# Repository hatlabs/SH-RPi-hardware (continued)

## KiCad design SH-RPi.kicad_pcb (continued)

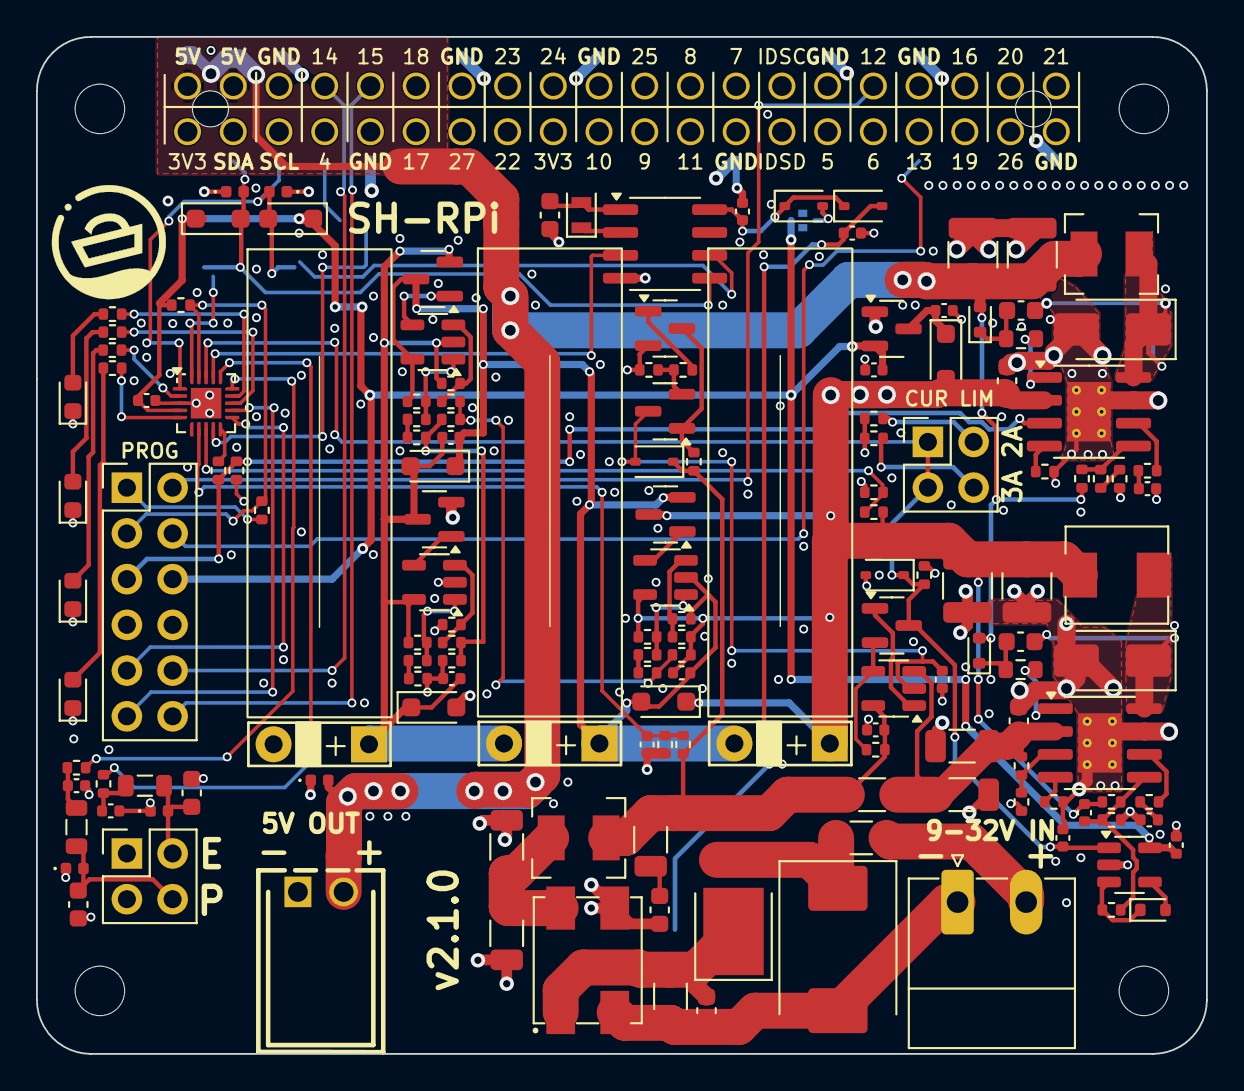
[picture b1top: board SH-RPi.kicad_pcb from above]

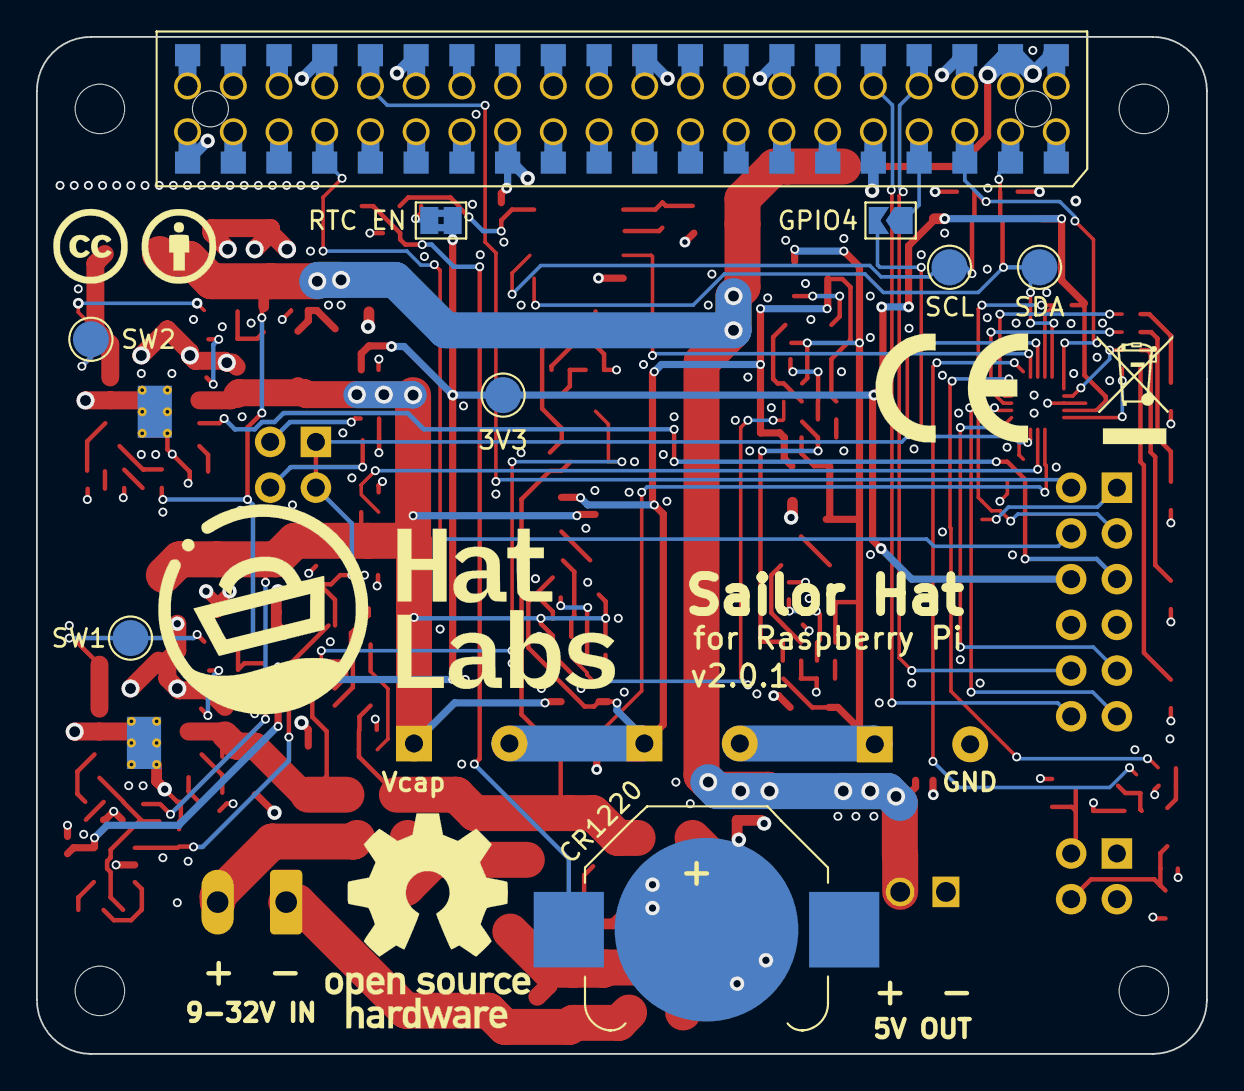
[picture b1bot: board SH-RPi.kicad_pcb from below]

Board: 4 copper layers, 65.0 x 56.5 mm, 168 parts (14 on the bottom side), 92 nets.

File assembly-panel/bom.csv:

Comment,Designator,Footprint,LCSC
Conn_01x02,J101,"Connector_Phoenix_MC:PhoenixContact_MC_1,5_2-G-3.81_1x02_P3.81mm_Horizontal",C8387
100nF,"C305,C306,C311,C312,C403,C406,C803,C1001,C1002,C1003",Capacitor_SMD:C_0402_1005Metric,C1525
10k,"R303,R311,R407,R409",Resistor_SMD:R_0402_1005Metric,C25744
56k,R401,Resistor_SMD:R_0402_1005Metric,C25796
2k,R404,Resistor_SMD:R_0402_1005Metric,C4109
20k,R403,Resistor_SMD:R_0402_1005Metric,C25765
150k,"R402,R1005,R1008,R1011",Resistor_SMD:R_0402_1005Metric,C93947
33pF 50V,"C401,C402",Capacitor_SMD:C_0603_1608Metric,C1663
33pF,"C404,C405",Capacitor_SMD:C_0402_1005Metric,C1562
GZ2012D601TF,"FB401,FB402",Inductor_SMD:L_0805_2012Metric,C1017
100R,"R308,R405,R406",Resistor_SMD:R_0402_1005Metric,C25076
ESD5451N,"D401,D402,D501,D503,D505",Diode_SMD:D_0402_1005Metric,C2936977
Conn_02x06_Odd_Even,J402,Connector_PinHeader_2.54mm:PinHeader_2x06_P2.54mm_Vertical,C5383107
1k,"R206,R408,R501,R502,R503,R504",Resistor_SMD:R_0402_1005Metric,C11702
100k,"R302,R410",Resistor_SMD:R_0402_1005Metric,C25741
ATtiny1616-MNR,U401,Package_DFN_QFN:VQFN-20-1EP_3x3mm_P0.4mm_EP1.7x1.7mm,C507118
Conn_02x02_Top_Bottom,J401,Connector_PinHeader_2.54mm:PinHeader_2x02_P2.54mm_Vertical,C492419
100nF,"C203,C308",Capacitor_SMD:C_0603_1608Metric,C14663
SLO0530H3R3MTT,L301,SH-RPi:L_MWSA0503S,C325963
47uF 16V,"C309,C310",Capacitor_SMD:C_1210_3225Metric,C77101
47k,R313,Resistor_SMD:R_0402_1005Metric,C25792
470k,R312,Resistor_SMD:R_0402_1005Metric,C137976
10m,R301,Resistor_SMD:R_1206_3216Metric,C105362
1N4148WT,"D201,D302,D305",Diode_SMD:D_SOD-523,C414017
5.1R,"R202,R309",Resistor_SMD:R_0603_1608Metric,C25197
68k,"R204,R307",Resistor_SMD:R_0402_1005Metric,C137947
SS56FL,D303,Diode_SMD:D_SMA,C122865
1uF 50V,C303,Capacitor_SMD:C_0603_1608Metric,C15849
10uF 50V,"C301,C302,C702,C703,C704,C705",Capacitor_SMD:C_1206_3216Metric,C13585
510R,R305,Resistor_SMD:R_0402_1005Metric,C25123
RT6365,"U201,U301",Package_SO:SOIC-8-1EP_3.9x4.9mm_P1.27mm_EP2.41x3.3mm_ThermalVias,C3024482
COS1333TR,U302,Package_TO_SOT_SMD:SOT-23-5,C693072
LMV321-TR,"U303,U1001,U1002,U1003",Package_TO_SOT_SMD:SOT-23-5,C3014306
1.5k,R310,Resistor_SMD:R_0402_1005Metric,C25867
BZT52C3V3S,"D301,D304",Diode_SMD:D_SOD-323,C173439
Conn_02x02,J301,Connector_PinHeader_2.54mm:PinHeader_2x02_P2.54mm_Vertical,C492419
3.9k,R316,Resistor_SMD:R_0402_1005Metric,C131467
300k,"R304,R1004,R1007,R1010,R1014,R1016,R1018",Resistor_SMD:R_0402_1005Metric,C25774
3.3k,R314,Resistor_SMD:R_0402_1005Metric,C25890
470pF,C304,Capacitor_SMD:C_0402_1005Metric,C1537
7.5k,R315,Resistor_SMD:R_0402_1005Metric,C137934
SW1,TP301,TestPoint:TestPoint_Pad_D2.0mm,
220nF,C307,Capacitor_SMD:C_0402_1005Metric,C16772
MMBT5551,"Q301,Q302",Package_TO_SOT_SMD:SOT-23,C2145
LBSS84LT1G,Q303,Package_TO_SOT_SMD:SOT-23,C8492
MBRA340T3G-FS,D202,Diode_SMD:D_SMA,C5563736
47uF 6.3V,"C204,C205",Capacitor_SMD:C_1210_3225Metric,C77101
51k,R201,Resistor_SMD:R_0402_1005Metric,C25794
27k,R203,Resistor_SMD:R_0402_1005Metric,C25771
4.7uF,C201,Capacitor_SMD:C_0603_1608Metric,C19666
3.3nF,C202,Capacitor_SMD:C_0402_1005Metric,C26404
FXL0420-1R0-M,"L201,L702",SH-RPi:L_MWSA0402,C167203
12k,R205,Resistor_SMD:R_0402_1005Metric,C25752
SW2,TP201,TestPoint:TestPoint_Pad_D2.0mm,
22pF C0G,C802,Capacitor_SMD:C_0603_1608Metric,C1653
1uF,C801,Capacitor_SMD:C_0402_1005Metric,C52923
Bridged,JP801,Jumper:SolderJumper-2_P1.3mm_Bridged2Bar_Pad1.0x1.5mm,
1N4148WS,"D801,D802",Diode_SMD:D_SOD-323,C2128
PCF8563T,U801,Package_SO:SOIC-8_3.9x4.9mm_P1.27mm,C7440
Conn_01x03,J801,SH-RPi:BatteryHolder_Myoung_MY-1220-03,C964818
X1A000061000200,Y801,Crystal:Crystal_SMD_2012-2Pin_2.0x1.2mm,C55208
5.0SMDJ33CA,D701,Diode_SMD:D_SMC,C2913642
12T.40000063AG12S1B02,F701,Fuse:Fuse_1206_3216Metric,C140479
1R,R701,Capacitor_SMD:C_0603_1608Metric,C22936
100nF 50V,C701,Capacitor_SMD:C_0603_1608Metric,C14663
PCAQ7060MW-102,L701,SH-RPi:L_CMF7060F,C2915648
10S45SP,D702,SH-RPi:SS5U100_TO-277,C2988031
Raspberry_Pi_2_3,J501,SH-RPi:PassthroughPinSocket_FH-00339_2x40_P2.54mm_Vertical_Bottom,C2685112
WHITE LED,"D506,D507,D508,D509",LED_SMD:LED_0603_1608Metric,C434422
Open,JP501,Jumper:SolderJumper-2_P1.3mm_Open_TrianglePad1.0x1.5mm,
1N5819WS,"D502,D504,D901,D1001,D1002,D1003",Diode_SMD:D_SOD-323_HandSoldering,C191023
Conn_01x02,J502,HL_Connector:CONN-TH_2P-P2.54_CONN-TH_2P-P2.54_,C2927503
SCL,TP502,TestPoint:TestPoint_Pad_D2.0mm,
SDA,TP501,TestPoint:TestPoint_Pad_D2.0mm,
1uF 16V,C901,Capacitor_SMD:C_0402_1005Metric,C52923
10uF 6.3V,C902,Capacitor_SMD:C_0402_1005Metric,C15525
3V3,TP901,TestPoint:TestPoint_Pad_D2.0mm,
HT7533-1,U901,Package_TO_SOT_SMD:SOT-23,C5279052
33k,"R1001,R1002,R1003",Resistor_SMD:R_0402_1005Metric,C25779
120k,"R1006,R1009,R1012",Resistor_SMD:R_0402_1005Metric,C93945
SS8050,"Q1001,Q1002,Q1003",Package_TO_SOT_SMD:SOT-23,C2150
330k,"R1013,R1015,R1017",Resistor_SMD:R_0402_1005Metric,C25778

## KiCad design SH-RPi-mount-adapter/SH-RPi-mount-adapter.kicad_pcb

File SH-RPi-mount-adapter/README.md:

# SH-RPi mount adapter

This directory contains a design for a Raspberry Pi mounting adapter. The adapter can be mounted to an enclosure using 3mm diameter adhesive standoffs. The Raspberry Pi goes on the adapter using M2.5 hexagonal brass standoffs and an M2.5 nut.

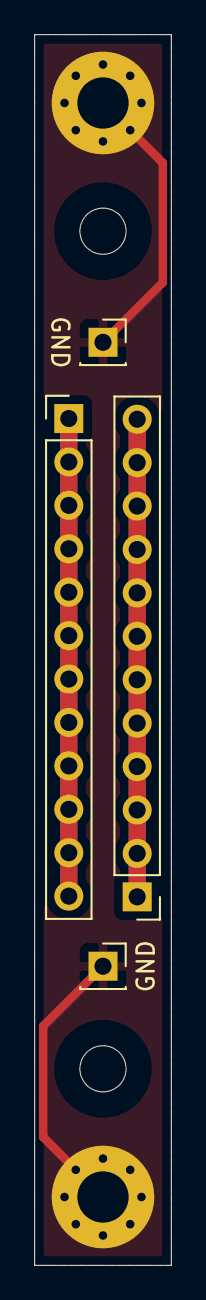
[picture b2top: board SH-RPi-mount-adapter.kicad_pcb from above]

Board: 2 copper layers, 8.0 x 72.0 mm, 8 parts (0 on the bottom side), 3 nets.

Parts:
H101, H102: MountingHole_Pad; MountingHole_3mm_Pad_Via
H103, H104: MountingHole; MountingHole_2.7mm_M2.5
J101, J102: Conn_01x01; PinSocket_1x01_P2.54mm_Vertical
J103, J104: Conn_01x12; PinHeader_1x12_P2.54mm_Vertical

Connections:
GND: H101.1, H102.1, J101.1, J102.1
unnamed: J103.1, J103.2, J103.3, J103.4, J103.5, J103.6, J103.7, J103.8, J103.9, J103.10, J103.11, J103.12
unnamed: J104.1, J104.2, J104.3, J104.4, J104.5, J104.6, J104.7, J104.8, J104.9, J104.10, J104.11, J104.12

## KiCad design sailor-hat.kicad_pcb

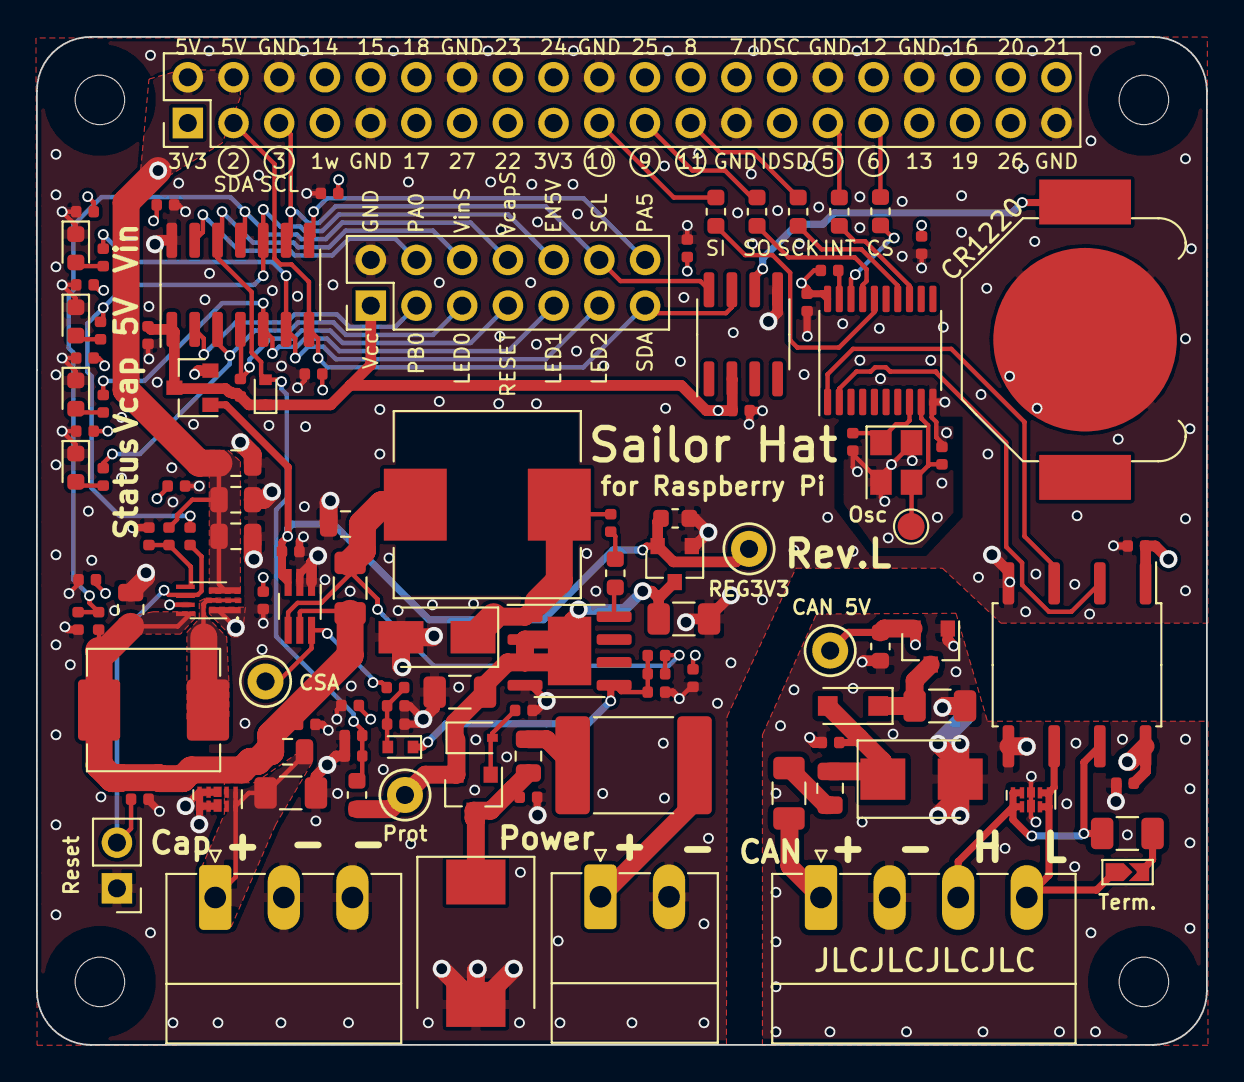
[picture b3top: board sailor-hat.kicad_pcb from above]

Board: 4 copper layers, 65.0 x 56.0 mm, 112 parts (0 on the bottom side), 63 nets.

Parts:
BT401: CR1220/3V; BatteryHolder_Linx_BAT-HLD-012-SMT
C201, C202, C203, C204, C305: 22uF/6.3V; C_0805_2012Metric
C301, C701: 10uF/50V; C_1206_3216Metric
C302, C802: 2.2uF/50V; C_1206_3216Metric
C303, C805: 2.2uF/16V; C_0603_1608Metric
C304, C307, C401, C601, C602, C806, C807, C808, C901, C902, C903, C904, C905, C906, C907, C908, C909, C910, C911, C912, C913, C914: 100nF; C_0402_1005Metric
C306: 12pF; C_0402_1005Metric
C308: 1nF; C_0402_1005Metric
C501, C801: 10nF/50V; C_0402_1005Metric
C702: 10uF; C_0402_1005Metric
C803, C804: 22pF; C_0402_1005Metric
D301: SS54F; D_SMA
D302, D601: PSBD521S-40; D_SOD-523
D501: 5.0SMDJ33CA; D_SMC
D502: MM3Z8V2; D_SOD-323
D602: BAT54C; SOT-23
D701, D703: GLED; LED_0603_1608Metric
D702, D704: RLED; LED_0603_1608Metric
D801: SMBJ33CA; D_SMB
D802: SM4007PL; D_SOD-123F
F501: ASMD2920-185; Fuse_2920_7451Metric
F801: SMD1206P010TF; Fuse_1206_3216Metric
FB501, FB701, FB801: GZ2012D601TF; L_0805_2012Metric
J501: Screw_Terminal_01x02; PhoenixContact_MC_1,5_2-G-3.81_1x02_P3.81mm_Horizontal
J601: Conn_02x07_Counter_Clockwise; PinHeader_2x07_P2.54mm_Vertical_CounterClockwise
J701: Screw_Terminal_01x03; PhoenixContact_MC_1,5_3-G-3.81_1x03_P3.81mm_Horizontal
J702: Raspberry_Pi_2_3; PinHeader_2x20_P2.54mm_Vertical
J801: Screw_Terminal_01x04; PhoenixContact_MC_1,5_4-G-3.81_1x04_P3.81mm_Horizontal
JP801: Term; SolderJumper-2_P1.3mm_Open_TrianglePad_Narrow
L201: MWSA0603-1R0MT; L_Abracon_ASPI-0630LR
L301: MWSA1004-150MT; L_Wuerth_HCI-1040
Q501: WST03P06; SOT-23
R201, R603, R802: 10k; R_0402_1005Metric
R202, R501: 100k; R_0402_1005Metric
R203, R604: 300k; R_0402_1005Metric
R204: 39k; R_0402_1005Metric
R301: 5.1; R_0603_1608Metric
R302: 470k; R_0402_1005Metric
R303: 220k; R_0402_1005Metric
R304: 20m; R_1206_3216Metric
R305: 15k; R_0402_1005Metric
R306: 7.5k; R_0402_1005Metric
R601: 62k; R_0603_1608Metric
R602, R701, R702, R703, R704: 2.2k; R_0402_1005Metric
R605: 200k; R_0402_1005Metric
R705, R706, R707, R708, R709: 0; R_0603_1608Metric
R801: 120R; R_1206_3216Metric
SW201: SW_SPST; PinHeader_1x02_P2.54mm_Vertical
TP301: REG3.3V; TestPoint_Keystone_5000-5004_Miniature
TP302: CSA; TestPoint_Keystone_5000-5004_Miniature
TP501: Vin_prot; TestPoint_Keystone_5000-5004_Miniature
TP801: OSC1; TestPoint_Pad_D1.5mm
TP802: CAN_5V; TestPoint_Keystone_5000-5004_Miniature
U201: TPS61022; TPS61022RWUR
U301: H7533-H#; SOT-23
U302: TX4138; SOIC-8-1EP_3.9x4.9mm_P1.27mm_EP2.41x3.81mm
U303: INA199A1DCKR; SOT-363_SC-70-6_Handsoldering
U401: DS3231MZ; SOIC-8_3.9x4.9mm_P1.27mm
U601: ATtiny841-SSU; SOIC-14_3.9x8.7mm_P1.27mm
U701, U801: RCLAMP0524P-N; Diodes_UDFN-10_1.0x2.5mm_P0.5mm
U802: H7550-H#; SOT-23
U803: MCP2515-xST; TSSOP-20_4.4x6.5mm_P0.65mm
U804: ISO1050DUB; SOP-8_6.62x9.15mm_P2.54mm
Y801: 1C208000CE0Q; Crystal_SMD_3225-4Pin_3.2x2.5mm

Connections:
5V: C202.1, C203.1, C204.1, J702.2, J702.4, R203.1, U201.3
+3V3: C806.1, C807.1, C901.1, C902.1, C903.1, C904.1, C905.1, C906.1, C907.1, C908.1, C909.1, C910.1, C911.1, C912.1, C913.1, C914.1, D602.2, J702.1, J702.17, R802.1, U803.20, U804.1
/ATT_LED0: J601.3, R704.1, U601.3
/ATT_LED1: J601.5, R703.1, U601.5
/ATT_LED2: J601.6, R701.1, U601.6
/ATT_Vcc: C401.1, C602.1, D601.1, D602.3, J601.1, R603.1, U401.2, U601.1
/Boost converter/ENIN: R201.2, R202.1, SW201.2, U201.5
/Boost converter/FB: R203.2, R204.1, U201.4
/Boost converter/SW: L201.2, U201.2
/Buck converter/BS: R301.2, U302.8
/Buck converter/CSAOUT: R305.1, TP302.1, U303.6
/Buck converter/FB: C306.2, D302.1, R302.2, R303.1, U302.5
/Buck converter/SW: C304.1, D301.1, L301.1, U302.1
/Buck converter/V_CSADIV: C308.1, D302.2, R305.2, R306.1
/Buck converter/Vout: C305.1, C306.1, L301.2, R302.1, R304.2, U303.4
/CANbus interface/CAN0_12V: F801.2, J801.1
/CANbus interface/CAN0_GND: C801.2, C802.2, C805.2, C808.2, D801.2, J801.2, U801.3, U801.8, U802.1, U804.5
/CANbus interface/CAN0_H: J801.3, R801.2, U801.1, U801.2, U801.9, U801.10, U804.7
/CANbus interface/CAN0_L: J801.4, JP801.1, U801.4, U801.5, U801.6, U801.7, U804.6
/CANbus interface/CAN12V_fused: C801.1, D801.1, D802.2, FB801.1
/CANbus interface/CAN12V_prot: C802.1, D802.1, U802.3
/CANbus interface/CAN_5V: C805.1, C808.1, TP802.1, U802.2, U804.8
/CANbus interface/CAN_RX: U803.2, U804.2
/CANbus interface/CAN_TX: U803.1, U804.3
/CANbus interface/OSC1: C804.1, TP801.1, U803.9, Y801.3
/CANbus interface/OSC2: C803.1, U803.8, Y801.1
/CANbus interface/RST: R802.2, U803.19
/CS0: R708.1, U803.18
/Control MCU/PA0: J601.13, U601.13
/Control MCU/PA5: J601.8, U601.8
/Control MCU/PB0: J601.2, U601.2
/Control MCU/RESET: J601.4, R603.2, U601.4
/Control MCU/VcapS: J601.11, R604.2, R605.1, U601.11
/Control MCU/VinS: C601.1, D601.2, J601.12, R601.2, R602.1, U601.12
/EN5V: J601.10, R201.1, R702.1, U601.10
/I/O/GPIO5: J702.29, R709.2
/I/O/GPIO6: J702.31, R708.2
/I/O/GPIO9: J702.21, R706.2
/I/O/GPIO10: J702.19, R705.2
/I/O/GPIO11: J702.23, R707.2
/I/O/Vcap_CONN: C701.1, FB701.2, J701.1, U701.4, U701.5, U701.6, U701.7
/INT0: R709.1, U803.13
/Protection/RP_G: D502.2, Q501.1, R501.1
/Protection/Vin: F501.2, J501.1
/Protection/Vin_fused: C501.1, D501.1, FB501.1, Q501.3
/RTC/VBAT: BT401.2, U401.6
/SCK: R707.1, U803.14
/SCL: J601.9, J702.5, U401.8, U601.9
/SDA: J601.7, J702.3, U401.7, U601.7
/SI: R705.1, U803.16
/SO: R706.1, U803.17
/Vcap: C201.1, C702.1, FB701.1, L201.1, R304.1, R604.1, U201.7, U303.5
/Vin_prot: C301.1, C302.1, D502.1, Q501.2, R601.1, TP501.1, U301.3, U302.2, U302.3, U302.9
GND: BT401.3, C201.2, C202.2, C203.2, C204.2, C301.2, C302.2, C303.2, C305.2, C307.1, C308.2, C401.2, C501.2, C601.2, C602.2, C701.2, C702.2, C803.2, C804.2, C806.2, C807.2, C901.2, C902.2, C903.2, C904.2, C905.2, C906.2, C907.2, C908.2, C909.2, C910.2, C911.2, C912.2, C913.2, C914.2, D301.2, D501.2, D701.1, D702.1, D703.1, D704.1, J501.2, J601.14, J701.2, J701.3, J702.6, J702.9, J702.14, J702.20, J702.25, J702.30, J702.34, J702.39, R202.2, R204.2, R303.2, R306.2, R501.2, R602.2, R605.2, SW201.1, U201.1, U201.6, U301.1, U302.4, U303.1, U303.2, U401.5, U601.14, U701.1, U701.2, U701.3, U701.8, U701.9, U701.10, U803.10, U804.4, Y801.2, Y801.4
unnamed: C304.2, R301.1
unnamed: D701.2, R701.2
unnamed: D702.2, R702.2
unnamed: D703.2, R703.2
unnamed: D704.2, R704.2
unnamed: F501.1, FB501.2
unnamed: F801.1, FB801.2
unnamed: JP801.2, R801.1
REG3.3V: C303.1, C307.2, D602.1, TP301.1, U301.2, U303.3

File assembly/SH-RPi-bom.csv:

Comment,Designator,Footprint,LCSC
"CR1220/3V","BT401","SH-RPi:BatteryHolder_Linx_BAT-HLD-012-SMT",""
"22uF/6.3V","C201,C202,C203,C204,C305","Capacitor_SMD:C_0805_2012Metric","C45783"
"10uF/50V","C301,C701","Capacitor_SMD:C_1206_3216Metric","C13585"
"2.2uF/50V","C302,C802","Capacitor_SMD:C_1206_3216Metric","C50254"
"2.2uF/16V","C303,C805","Capacitor_SMD:C_0603_1608Metric","C23630"
"100nF","C304,C307,C401,C601,C602,C806,C807,C808,C901,C902,C903,C904,C905,C906,C907,C908,C909,C910,C911,C912,C913,C914","Capacitor_SMD:C_0402_1005Metric","C1525"
"12pF","C306","Capacitor_SMD:C_0402_1005Metric","C1547"
"1nF","C308","Capacitor_SMD:C_0402_1005Metric","C1523"
"10nF/50V","C501,C801","Capacitor_SMD:C_0402_1005Metric","C15195"
"10uF","C702","Capacitor_SMD:C_0402_1005Metric","C15525"
"22pF","C803,C804","Capacitor_SMD:C_0402_1005Metric","C1555"
"SS54F","D301","Diode_SMD:D_SMA","C64882"
"PSBD521S-40","D302,D601","Diode_SMD:D_SOD-523","C168633"
"5.0SMDJ33CA","D501","Diode_SMD:D_SMC","C112941"
"MM3Z8V2","D502","Diode_SMD:D_SOD-323","C118606"
"BAT54C","D602","Package_TO_SOT_SMD:SOT-23","C37704"
"GLED","D701,D703","LED_SMD:LED_0603_1608Metric","C72043"
"RLED","D702,D704","LED_SMD:LED_0603_1608Metric","C2286"
"SMBJ33CA","D801","Diode_SMD:D_SMB","C143164"
"SM4007PL","D802","Diode_SMD:D_SOD-123F","C64898"
"ASMD2920-185","F501","Fuse:Fuse_2920_7451Metric","C135379"
"SMD1206P010TF","F801","Fuse:Fuse_1206_3216Metric","C20981"
"GZ2012D601TF","FB501,FB701,FB801","Inductor_SMD:L_0805_2012Metric","C1017"
"Screw_Terminal_01x02","J501","Connector_Phoenix_MC:PhoenixContact_MC_1,5_2-G-3.81_1x02_P3.81mm_Horizontal","C8387"
"Conn_02x07_Counter_Clockwise","J601","SH-RPi:PinHeader_2x07_P2.54mm_Vertical_CounterClockwise","C492424"
"Screw_Terminal_01x03","J701","Connector_Phoenix_MC:PhoenixContact_MC_1,5_3-G-3.81_1x03_P3.81mm_Horizontal","C8387"
"Raspberry_Pi_2_3","J702","Connector_PinHeader_2.54mm:PinHeader_2x20_P2.54mm_Vertical",""
"Screw_Terminal_01x04","J801","Connector_Phoenix_MC:PhoenixContact_MC_1,5_4-G-3.81_1x04_P3.81mm_Horizontal","C7245"
"Term","JP801","SH-RPi:SolderJumper-2_P1.3mm_Open_TrianglePad_Narrow",""
"MWSA0603-1R0MT","L201","Inductor_SMD:L_Abracon_ASPI-0630LR","C112125"
"MWSA1004-150MT","L301","Inductor_SMD:L_Wuerth_HCI-1040","C151872"
"WST03P06","Q501","Package_TO_SOT_SMD:SOT-23","C105166"
"10k","R201,R603,R802","Resistor_SMD:R_0402_1005Metric","C25744"
"100k","R202,R501","Resistor_SMD:R_0402_1005Metric","C25741"
"300k","R203,R604","Resistor_SMD:R_0402_1005Metric","C25774"
"39k","R204","Resistor_SMD:R_0402_1005Metric","C25783"
"5.1","R301","Resistor_SMD:R_0603_1608Metric","C25197"
"470k","R302","Resistor_SMD:R_0402_1005Metric","C25790"
"220k","R303","Resistor_SMD:R_0402_1005Metric","C25767"
"20m","R304","Resistor_SMD:R_1206_3216Metric","C127690"
"15k","R305","Resistor_SMD:R_0402_1005Metric","C25756"
"7.5k","R306","Resistor_SMD:R_0402_1005Metric","C25918"
"62k","R601","Resistor_SMD:R_0603_1608Metric","C23221"
"2.2k","R602,R701,R702,R703,R704","Resistor_SMD:R_0402_1005Metric","C25879"
"200k","R605","Resistor_SMD:R_0402_1005Metric","C25764"
"0","R705,R706,R707,R708,R709","Resistor_SMD:R_0603_1608Metric","C21189"
"120R","R801","Resistor_SMD:R_1206_3216Metric","C17909"
"SW_SPST","SW201","Connector_PinHeader_2.54mm:PinHeader_1x02_P2.54mm_Vertical",""
"REG3.3V","TP301","TestPoint:TestPoint_Keystone_5000-5004_Miniature",""
"CSA","TP302","TestPoint:TestPoint_Keystone_5000-5004_Miniature",""
"Vin_prot","TP501","TestPoint:TestPoint_Keystone_5000-5004_Miniature",""
"OSC1","TP801","TestPoint:TestPoint_Pad_D1.5mm",""
"CAN_5V","TP802","TestPoint:TestPoint_Keystone_5000-5004_Miniature",""
"TPS61022","U201","SH-RPi:TPS61022RWUR",""
"H7533-H#","U301","Package_TO_SOT_SMD:SOT-23","C277872"
"TX4138","U302","Package_SO:SOIC-8-1EP_3.9x4.9mm_P1.27mm_EP2.41x3.81mm","C329267"
"INA199A1DCKR","U303","Package_TO_SOT_SMD:SOT-363_SC-70-6_Handsoldering","C59135"
"DS3231MZ","U401","Package_SO:SOIC-8_3.9x4.9mm_P1.27mm","C107410"
"ATtiny841-SSU","U601","Package_SO:SOIC-14_3.9x8.7mm_P1.27mm","C219103"
"RCLAMP0524P-N","U701,U801","Package_DFN_QFN:Diodes_UDFN-10_1.0x2.5mm_P0.5mm","C316044"
"H7550-H#","U802","Package_TO_SOT_SMD:SOT-23","C277875"
"MCP2515-xST","U803","Package_SO:TSSOP-20_4.4x6.5mm_P0.65mm","C15193"
"ISO1050DUB","U804","Package_SO:SOP-8_6.62x9.15mm_P2.54mm","C16428"
"1C208000CE0Q","Y801","Crystal:Crystal_SMD_3225-4Pin_3.2x2.5mm","C133366"

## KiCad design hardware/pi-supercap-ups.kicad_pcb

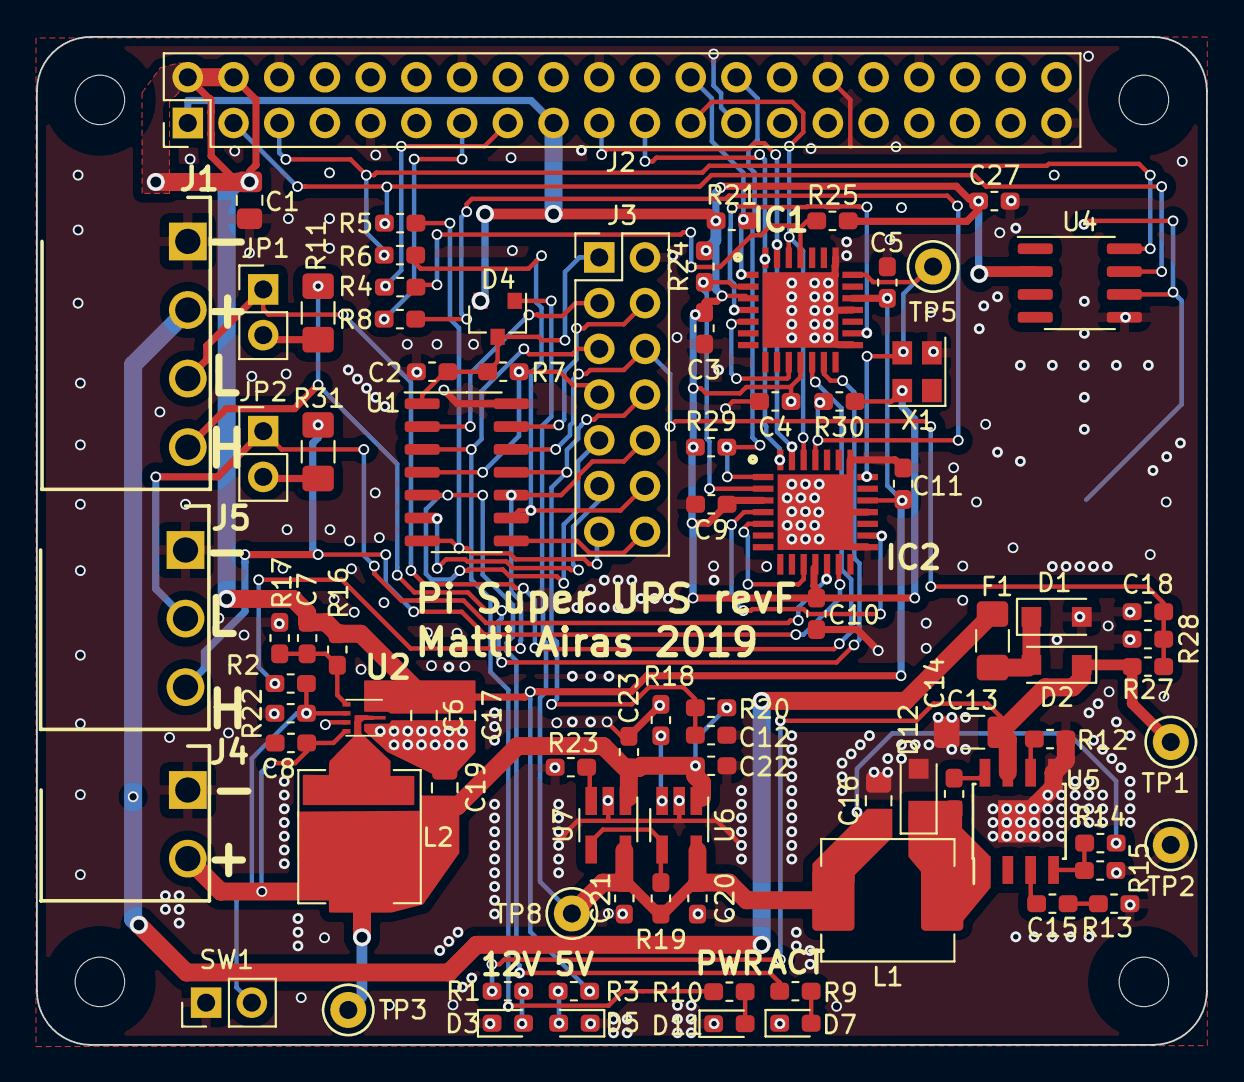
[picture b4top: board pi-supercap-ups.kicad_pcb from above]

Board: 2 copper layers, 65.0 x 56.0 mm, 88 parts (1 on the bottom side), 61 nets.

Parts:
BT1: CR1220 3V; BatteryHolder_Linx_BAT-HLD-012-SMT
C1, C6, C17: 47uF 10V; C_0805_2012Metric_Pad1.15x1.40mm_HandSolder
C2, C3, C4, C5, C9, C10, C11, C12, C14, C18, C27: 100nF; C_0603_1608Metric_Pad1.05x0.95mm_HandSolder
C7: 220p; C_0603_1608Metric_Pad1.05x0.95mm_HandSolder
C8: 100n; C_0603_1608Metric_Pad1.05x0.95mm_HandSolder
C13: 10uF 50V; C_1206_3216Metric_Pad1.42x1.75mm_HandSolder
C15: 150pF; C_0603_1608Metric_Pad1.05x0.95mm_HandSolder
C16, C19: 47uF 6.3V; C_0805_2012Metric_Pad1.15x1.40mm_HandSolder
C20, C21, C22, C23: 10uF 10V; C_0603_1608Metric_Pad1.05x0.95mm_HandSolder
D1: SMF16CA; D_SOD-123F
D2, D12: DS34W; D_SOD-123F
D3, D5, D11: RLED; LED_0603_1608Metric_Pad1.05x0.95mm_HandSolder
D4: BAT54C; SOT-23
D7: GLED; LED_0603_1608Metric_Pad1.05x0.95mm_HandSolder
F1: 1A; Fuse_1206_3216Metric_Pad1.42x1.75mm_HandSolder
IC1, IC2: MCP25625T-E_ML; QFN65P600X600X100-29M-D
J1: Screw_Terminal_01x04; TerminalBlock_WJ15EDGRC-3.81-4P
J2: Raspberry_Pi_2_3; PinHeader_2x20_P2.54mm_Vertical
J3: Conn_02x07_Counter_Clockwise; PinHeader_2x07_P2.54mm_Vertical_CounterClockwise
J4: Screw_Terminal_01x02; TerminalBlock_WJ15EDGRC-3.81-2P
J5: Screw_Terminal_01x03; TerminalBlock_WJ15EDGRC-3.81-3P
JP1, JP2: Term; PinHeader_1x02_P2.54mm_Vertical
L1: 10uH 3.5A; L_Abracon_ASPI-0630LR
L2: 1uH; L_Abracon_ASPI-0630LR
R1: 4.7k; R_0603_1608Metric_Pad1.05x0.95mm_HandSolder
R2, R7, R19, R21, R24, R25, R28, R29, R30: 10k; R_0603_1608Metric_Pad1.05x0.95mm_HandSolder
R3: 2.2k; R_0603_1608Metric_Pad1.05x0.95mm_HandSolder
R4, R5, R6, R8: 0; R_0603_1608Metric_Pad1.05x0.95mm_HandSolder
R9, R10: 1.5k; R_0603_1608Metric_Pad1.05x0.95mm_HandSolder
R11, R31: 120R; R_1206_3216Metric_Pad1.42x1.75mm_HandSolder
R12: 200k; R_0603_1608Metric_Pad1.05x0.95mm_HandSolder
R13: 54.9k; R_0603_1608Metric_Pad1.05x0.95mm_HandSolder
R14: 93k; R_0603_1608Metric_Pad1.05x0.95mm_HandSolder
R15: 40.2k; R_0603_1608Metric_Pad1.05x0.95mm_HandSolder
R16: 330k; R_0603_1608Metric_Pad1.05x0.95mm_HandSolder
R17: 43k; R_0603_1608Metric_Pad1.05x0.95mm_HandSolder
R18, R23: 4.53k; R_0603_1608Metric_Pad1.05x0.95mm_HandSolder
R20, R22: 100k; R_0603_1608Metric_Pad1.05x0.95mm_HandSolder
R27: 51k; R_0603_1608Metric_Pad1.05x0.95mm_HandSolder
SW1: SW_SPST; PinHeader_1x02_P2.54mm_Vertical
TP1: +12V_prot; TestPoint_Keystone_5000-5004_Miniature
TP2: GND; TestPoint_Keystone_5000-5004_Miniature
TP3: Vcap; TestPoint_Keystone_5000-5004_Miniature
TP5: OSC; TestPoint_Keystone_5000-5004_Miniature
TP8: Vbuck; TestPoint_Keystone_5000-5004_Miniature
U1: ATtiny44-20SSU; SOIC-14_3.9x8.7mm_P1.27mm
U2: TPS61022; TPS61022RWUR
U4: DS3231MZ; SOIC-8_3.9x4.9mm_P1.27mm
U5: MP1584EN; SOIC-8-1EP_3.9x4.9mm_P1.27mm_EP2.35x2.35mm
U6, U7: MT9700; SOT-23-5_HandSoldering
X1: S3D8.000000B20F30T; Oscillator_SMD_Abracon_ASE-4Pin_3.2x2.5mm

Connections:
2.65V: C16.1, C20.1, C21.1, D4.1, L1.2, R14.2, R19.1, TP8.1, U6.5, U7.5
3.3V: C3.1, C4.1, C9.1, C10.1, C27.1, D4.2, IC1.3, IC1.11, IC2.3, IC2.11, J2.1, J2.17, R21.1, R24.2, R25.1, R29.1, R30.1, U4.2, X1.4
5V: C1.1, C5.1, C6.1, C7.1, C11.1, C17.1, IC1.19, IC2.19, J2.2, J2.4, R3.1, R16.1, U2.3
+12V: F1.2, J1.2
/12V_fused: D1.1, D2.2, F1.1
/ATT_LED0: J3.3, R10.1, U1.3
/ATT_LED1: J3.5, R9.1, U1.5
/ATT_RESET: J3.4, R7.2, U1.4
/ATT_Vcc: C2.1, D4.3, J3.1, R7.1, U1.1
/Boost converter/FB: C7.2, R16.2, R17.1, U2.4
/Boost converter/SW: L2.2, U2.2
/Buck converter/BST: C14.2, U5.8
/Buck converter/COMP: C15.1, U5.3
/Buck converter/FB: R14.1, R15.1, U5.4
/Buck converter/FREQ: R12.1, U5.6
/Buck converter/SW: C14.1, D12.1, L1.1, U5.1
/CAN0_H: IC1.13, J1.4, R11.2
/CAN0_L: IC1.12, J1.3, JP1.1
/CAN1_H: IC2.13, J5.3, R31.2
/CAN1_L: IC2.12, J5.2, JP2.1
/CANbus interface/OSC_OUT: IC1.21, IC2.21, TP5.1, X1.3
/CANbus interface/~RESET: IC1.2, IC2.2, R24.1
/CS0: IC1.1, J2.24, R21.2
/CS1: IC2.1, J2.26, R29.2
/EN5V: J3.10, R2.1, U1.10
/GPIO2: J2.3, R5.2, U4.7
/GPIO3: J2.5, R6.2, U4.8
/GPIO22: J2.15, R4.2
/GPIO27: J2.13, R8.2
/INT0: IC1.25, R4.1, R25.2
/INT1: IC2.25, R8.1, R30.2
/PA0: J3.13, U1.13
/PA5: J3.8, U1.8
/PA7: J3.6, U1.6
/PB0: J3.2, U1.2
/RTC/VBAT: BT1.1, U4.6
/SCK: IC1.26, IC2.26, J2.23
/SCL: J3.9, R6.1, U1.9
/SDA: J3.7, R5.1, U1.7
/SI: IC1.27, IC2.27, J2.19
/SO: IC1.28, IC2.28, J2.21
/V12:6: C18.1, J3.12, R27.2, R28.1, U1.12
/Vcap: C8.1, C19.1, C22.1, C23.1, J4.2, L2.1, R20.1, TP3.1, U2.7, U6.1, U7.1
/VcapS: C12.1, J3.11, R20.2, U1.11
/Vin: C13.1, D2.1, R1.1, R27.1, TP1.1, U5.7
GND: BT1.2, C1.2, C2.2, C3.2, C4.2, C5.2, C6.2, C8.2, C9.2, C10.2, C11.2, C12.2, C13.2, C16.2, C17.2, C18.2, C19.2, C20.2, C21.2, C22.2, C23.2, C27.2, D1.2, D3.1, D5.1, D7.1, D11.1, D12.2, IC1.15, IC1.18, IC1.22, IC1.29, IC2.15, IC2.18, IC2.22, IC2.29, J1.1, J2.6, J2.9, J2.14, J2.20, J2.25, J2.30, J2.34, J2.39, J3.14, J4.1, J5.1, R12.2, R13.2, R15.2, R17.2, R18.2, R22.2, R23.2, R28.2, SW1.1, TP2.1, U1.14, U2.1, U2.6, U4.5, U5.5, U5.9, U6.2, U7.2, X1.2
unnamed: C15.2, R13.1
unnamed: D3.2, R1.2
unnamed: D5.2, R3.2
unnamed: D7.2, R9.2
unnamed: D11.2, R10.2
unnamed: IC1.5, IC1.10
unnamed: IC1.4, IC1.16
unnamed: IC2.5, IC2.10
unnamed: IC2.4, IC2.16
unnamed: JP1.2, R11.1
unnamed: JP2.2, R31.1
unnamed: R2.2, R22.1, SW1.2, U2.5
unnamed: R18.1, U6.3
unnamed: R19.2, U6.4, U7.4
unnamed: R23.1, U7.3

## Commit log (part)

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2018-12-14 basic implementation
2018-12-14 correct port et al
2018-12-14 daemonization
2018-12-15 log via syslog
2018-12-15 increase timeout to 10 seconds
2018-12-15 rewrote to use RPi.GPIO directly
2018-12-16 improved syslog formatting
2018-12-16 added a systemd service file
2018-12-16 provided installation instructions
2018-12-16 fix log formatting
2018-12-16 added the schematics file and a schematics picture
2018-12-16 add a comment about the sample circuit in README
2019-01-17 Rename to pi-super-ups
2019-01-17 add setup.py, argument parsing
2019-01-17 shouldn't use nargs=1
2019-02-15 Move service sources to src
2019-02-15 remove old proto schematics files
2019-02-15 Added hardware schematics to the project
2019-02-15 Add a bit of readme and a picture of PCB layout.
2019-02-15 Add a hardware license.
2019-03-09 Initial Attiny13a firmware code
2019-03-09 watchdog pin logic updated
2019-03-09 firmware works now
2019-03-09 added a pull-up resistor to ATtiny reset pin
2019-03-11 ignore blackout on startup (possibly a faulty setup)
2019-03-13 Fix comment on GPIO initial state.
2019-03-13 Add an output cap to the MT3608.
2019-03-14 use level detection instead of edge detection to prevent erroneous events due to noise and slow switching times
2019-04-20 Reduce attiny13 firmware writing speed
2019-04-20 Implement next hardware revision
2019-05-13 fix a silk screen error by swapping R14 and R15
2019-08-17 Changed to pure-serial topology. Changed to beefier mcu.
2019-09-01 Layout partially done before change of plans
2019-09-10 add .gitignore to firmware
2019-09-10 revE ready for production
2019-09-29 Fixed wrong footprints & passive component values.
2019-09-30 Redesign SMPS layouts.
2019-10-16 C7 is not required and can be made virtual
2019-10-31 Fix platformio environment name
2019-10-31 Add ENIN trace to the PCB. Change input voltage dividers for 1.1V ref.
2019-10-31 Update monitor daemon to match the new firmware
2019-10-31 New I2C firmware implementation
2020-01-08 Fix component values etc
2020-01-10 Move contents from hardware/ to repo root
2020-01-10 Rename to Sailor Hat
2020-01-10 Software license not needed for this repository
2020-01-10 Only discuss hardware in the README
2020-01-14 Update MCU to ATtiny841
2020-01-17 Implement better current limiting
2020-01-17 Add test points for new features
2020-01-17 Annotate and tweak power flags
2020-01-20 Add graphics to PCB silk screen
2020-01-20 Update licence, tweaks to footprints and ERC
2020-01-22 Update the README, add a new rendered image of the board
2020-01-23 Tweaked net naming
2020-02-27 Need a cap to cool down current limiting FB loop
2020-02-27 Move D6 label
2020-02-29 Fix diode footprint
2020-02-29 Prevent reverse current through regulator
2020-02-29 Make protection TVS bidirectional
2020-02-29 Swap CAN0 and CAN1 connectors; use GPIO 5 & 6 for CAN interrupts for Moitessier compatibility
2020-02-29 Implement revH changes in PCB
2020-03-01 Add a voltage divider for indicating HW version
2020-03-09 Add LCSC part numbers to components
2020-03-09 Make unpopulated CAN0 components virtual
2020-04-07 Update parts according to JLCPCB availability
2020-08-12 Modify current limiting threshold
2020-08-19 Isolated CAN bus implementation
2020-08-19 Optimize PCB layout; add missing filter caps
2020-08-20 Parts updated to match JLCPCB availability
2020-09-03 Revert back to using INA199 as a current limiter
2020-09-03 Make voltage protection circuitry 24V compliant
2020-09-03 Cram all new stuff on the PCB
2020-09-03 Swap CAN power rectifier diode into a smaller one
2020-09-03 Update components according to JLCPCB availability
2020-11-12 Schema updated
2020-11-16 Redesigned layout to take EMC issues better into account
2020-11-16 Add the all-important HL logo
2020-11-17 Fix DRC errors
2020-11-19 Change CAN termination jumper to a solder jumper
2020-11-19 Flipped the battery to the top side of the board
2020-11-26 Make power connector identical to SH-ESP32 for consistency
2020-11-26 Nudge GPIO connector silk screen legend a bit down
2020-11-26 Add missing LCSC part numbers
2020-11-26 Update the README and the images
2020-11-27 Extend the pads to make hand soldering easier
2020-11-27 Make power traces around DC-DC converters as wide as possible
    Some traces also converted to fill areas
2020-11-27 Update the README to point to the new location
2020-11-27 Rename project files to follow the conventions in SH-ESP32
2020-11-27 Set solder mask min width to 0
2020-11-27 Updated the title block and one THT terminal part number
2020-11-27 Update the BAT54C part number according to availability
2020-11-27 Add assembly files
2020-12-10 Extend the PCB size to provide space for an onboard supercapacitor
    The PCB was extended to the left by 21mm to provide room for a
    18x40mm (max 18x42mm) 50/60F supercapacitor. The supercapacitor
    is lodged in a slot on the PCB to provide mechanical stability and limit
    the maximum height of the assembly. It now requires 14mm of headroom.
    Additionally, the following changes were made:
    - the external supercap connector was removed
2020-12-16 Route I2C to unique pins
    Also:
    - Connect RTC interrupt to ATtiny
    - Break out the interrupt pin to a connector for external signaling
2020-12-17 Split the 120R CAN termination resistor into two 240R
    Increase the thermal clearances on copper fills
2020-12-19 Change the MCU to ATTiny1614
    Also:
    - Rewired the PCB due to changed pins
    - Cleaned up network names around the MCU
    - Use a basic part Schottky for the buck converter
    - Change MCP2515 crystal to 16MHz basic part
    - Change BAT54C to two discrete schottkys
2020-12-19 Fixed the VCap trace and fill
2020-12-19 Improved LED traces to allow more continuous ground frame around the supercap slot
2021-01-29 Remove CAN bus RCLAMP (N2K spec requires that +-18V can be connected to any input)
2021-01-29 Replace polyfuse with a regular fuse
2021-02-01 Modify boost stage design according to WEBENCH results
2021-02-03 IN PROGRESS
2021-02-04 Buck stage redesigned with a new IC and current limiter
2021-02-06 Buck converter changed to LMR16030
2021-02-07 Finish PCB layout updates
2021-02-08 Remove undersized ferrite bead, shuffle power protection circuitry
    Also add new logo & generic cleanup
2021-02-08 Update release utility files
2021-02-08 Update title blocks
2021-02-08 Round supercap slot edges a bit more
2021-02-08 Change ground pads to power input
2021-02-08 Add JLCPCB tooling holes
2021-02-08 Add rotation info for the LMR16330 footprint
2021-02-08 Change boost FB resistors to JLC basic ones
2021-02-15 Add LCSC part number for the boost converter
2021-02-19 Add a note for the new mystery hole
2021-02-19 Add an LCSC part no. for the battery clip
2021-02-19 Update README images
2021-03-24 Replace current limiting op amp with a RRIO one
2021-03-26 Update the current limiter design and swap the signal diodes
2021-03-26 Switch to LMR14050
2021-03-26 Bump Vin fuse to 2.5A
2021-03-26 Remove rescue files from repo
2021-03-27 Revert I2C pins back to defaults
    - What was I thinking?
    - Also improve silk screen labeling around headers and connectors
2021-03-27 Add HL logo, change versioning scheme
2021-03-27 Change versioning scheme in the schema files
2021-03-27 Add a 5V header for fans etc
2021-03-29 Tweak components according to JLCPCB availability
2021-04-15 shouldn't include assembly files in master branch
2021-04-15 Bump version number to 1.0.0
2021-04-15 Add the WEEE logo
2021-04-16 Reformat and update README.md
2021-04-18 Add missing image
2021-04-18 Add the mount adapter design
2021-05-14 Add links to the documentation website and hatlabs.fi.
2021-08-19 Tweak a text box comment to make it more accurate
2021-08-19 Update parts according to availability
2021-08-19 Bump version, update license
2021-11-18 Switch to KiCad 6
2021-11-18 Fix broken symbols
2021-11-18 Apply schema changes to the PCB
2021-11-18 Revert the Rev. 1.0.1 LDO change
    The new part exhibited severe startup overshoot
    which disabled or even damaged the MCU.
2021-11-18 Remove cruft from previous version
2021-11-18 Remove leftover footprint libraries
2021-11-18 Migrate symbol libraries to KiCad 6
2022-09-18 Save with KiCad 6.0.7
2022-09-18 Remove the CAN bus interface
2022-09-18 Change the power supply topology
2022-10-14 SH-RPi v2 schematic design
2022-10-16 Remove an obsolete rescue file
2022-10-16 Remove an obsolete schematics file
2022-10-16 Add footprints
2022-10-16 Remove the unused mount adapter design
2022-10-16 Remove old rendered images
2022-10-16 Add auto-generated backups to .gitignore
2022-10-16 WIP: Assign footprints and LCSC part numbers
2022-10-16 Remove a duplicate Footprint entry
2022-10-16 Use a battery clip instead of a cell
2022-10-16 Assign footprints and part numbers to components
2022-10-18 WIP: PCB layout
2022-10-18 Re-add cc-by silkscreen logo
2022-10-18 Add a Pi mounting hole footprint
2022-10-18 Re-add XH style connector footprints
2022-10-18 Initial PCB component layout done
2022-10-18 Adjust the battery clip and LED positions
2022-10-19 Finish PCB routing
2022-10-19 Update footprint 3D model paths
2022-10-19 Add more reference vias and barrier around the oscillator
2022-10-21 Replace "ideal diode" with Schottky & other changes
2022-10-24 Add Kikit footprints
2022-10-24 Redesign the EMI input filter
2022-10-25 Remove silk screen graphics from the BOM
2022-10-25 Exclude supercaps and graphics from BOM and POS files
2022-10-25 Add KiKit tab markers to the PCB
2022-10-25 Final tweaks to buck converter layouts etc
2022-10-25 Update title block date for schematic and pcb
2022-11-26 Fix LDO reference font size
2022-12-06 Remove connection to GPIO 3.3V
2022-12-06 Update current limiter according to tests
2022-12-06 Update stage 2 output caps
2022-12-06 Update LED GPIO pins to allow PWM output
2022-12-06 Update passthrough socket footprint
2022-12-06 Pick LCSC part numbers for changed components
2022-12-09 Move LDO schottkys to the input side
2022-12-09 WIP PCB
2022-12-18 Add 2x10uF input caps to stage 1
2022-12-19 Insert additional input caps to reduce conducted noise
2022-12-23 Tweak the layout and reroute tracks
2022-12-26 Add test points, test footprints, GND vias
2022-12-26 Update title block data
2022-12-26 Change stage 1 diode to SSL56F
2022-12-28 Change stage 2 switching diode
2022-12-28 Add optional connection to Raspi GPIO4
2022-12-28 Flip the pass through connector to bottom side
2022-12-28 Add missing footprints and 3d models
2022-12-28 Exclude empty footprints from POS file
2022-12-28 Increase copper edge clearance to 0.4 mm
2022-12-28 Remove mounting holes from BOM
2022-12-28 Add assembly scripts to repo
2022-12-28 Ignore supercaps in JLCPCB BOM
2022-12-28 Update passthrough socket footprint to fit in copper area
2022-12-28 Add a full frame to meet JLC minimum size requirements
2022-12-28 Change stage 1 switching diode due to part availability
2022-12-28 Fix J301 part number
2023-01-15 Remove debugging pads
2023-01-15 Increase passthrough conx pad clearance
2023-01-15 Bump board version number
2023-01-28 Rename passthrough connectors to include the connector type
2023-01-28 Replace the GPIO connector with FH-00339
2023-01-28 Update the panelization script to have fixed v-cuts
2023-01-28 Remove KiKit tab markers from the PCB
2023-01-28 Add FH-00339 passthrough connector footprint
2023-01-28 Update title block dates
2023-01-28 Correct part LCSC codes and values
2023-01-30 Remove solder paste from the battery holder center mask
2023-02-15 v2.0.0
2023-03-02 Add final assembly files
2023-08-02 Update C312 and R306
    These changes fix the too high startup voltage and the first stage
    buck converter stability issues.
2023-08-22 Update panel assembly script
2023-09-18 Update the README
2024-08-10 Add a STEP model of the SH-RPi
2024-09-25 Move rotation definitions to component fields
2024-09-25 Fix the passthrough socket footprint
2024-09-25 Add a footprint for a huge polyfuse
2024-09-25 Add an improved .gitignore file
2024-09-25 Add lock files to .gitignore
2024-09-25 Update footprints
2024-11-17 Rename power input sheets
    Also tweak pass-through connector solder paste margins.
